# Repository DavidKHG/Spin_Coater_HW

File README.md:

# Spin_Coater_HW
- Final components for spin coater such as circuit, sensor, display, mechanical design.

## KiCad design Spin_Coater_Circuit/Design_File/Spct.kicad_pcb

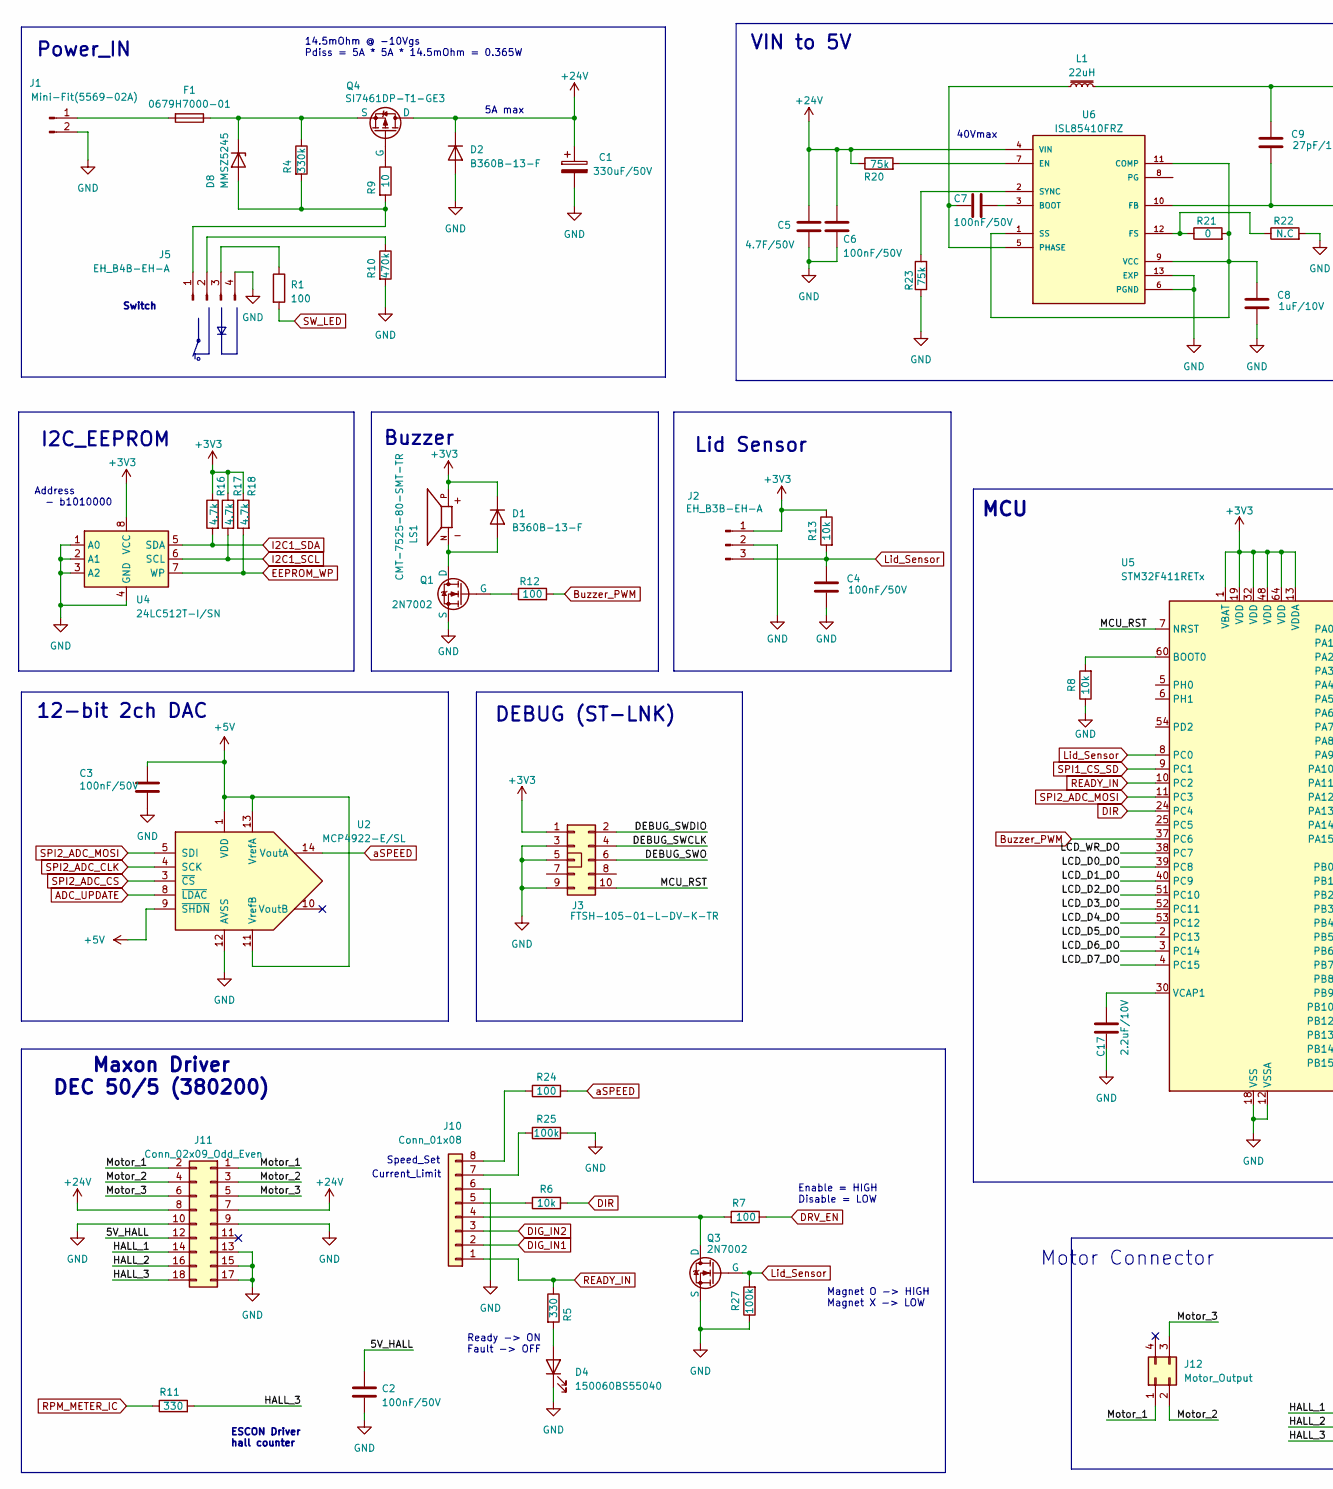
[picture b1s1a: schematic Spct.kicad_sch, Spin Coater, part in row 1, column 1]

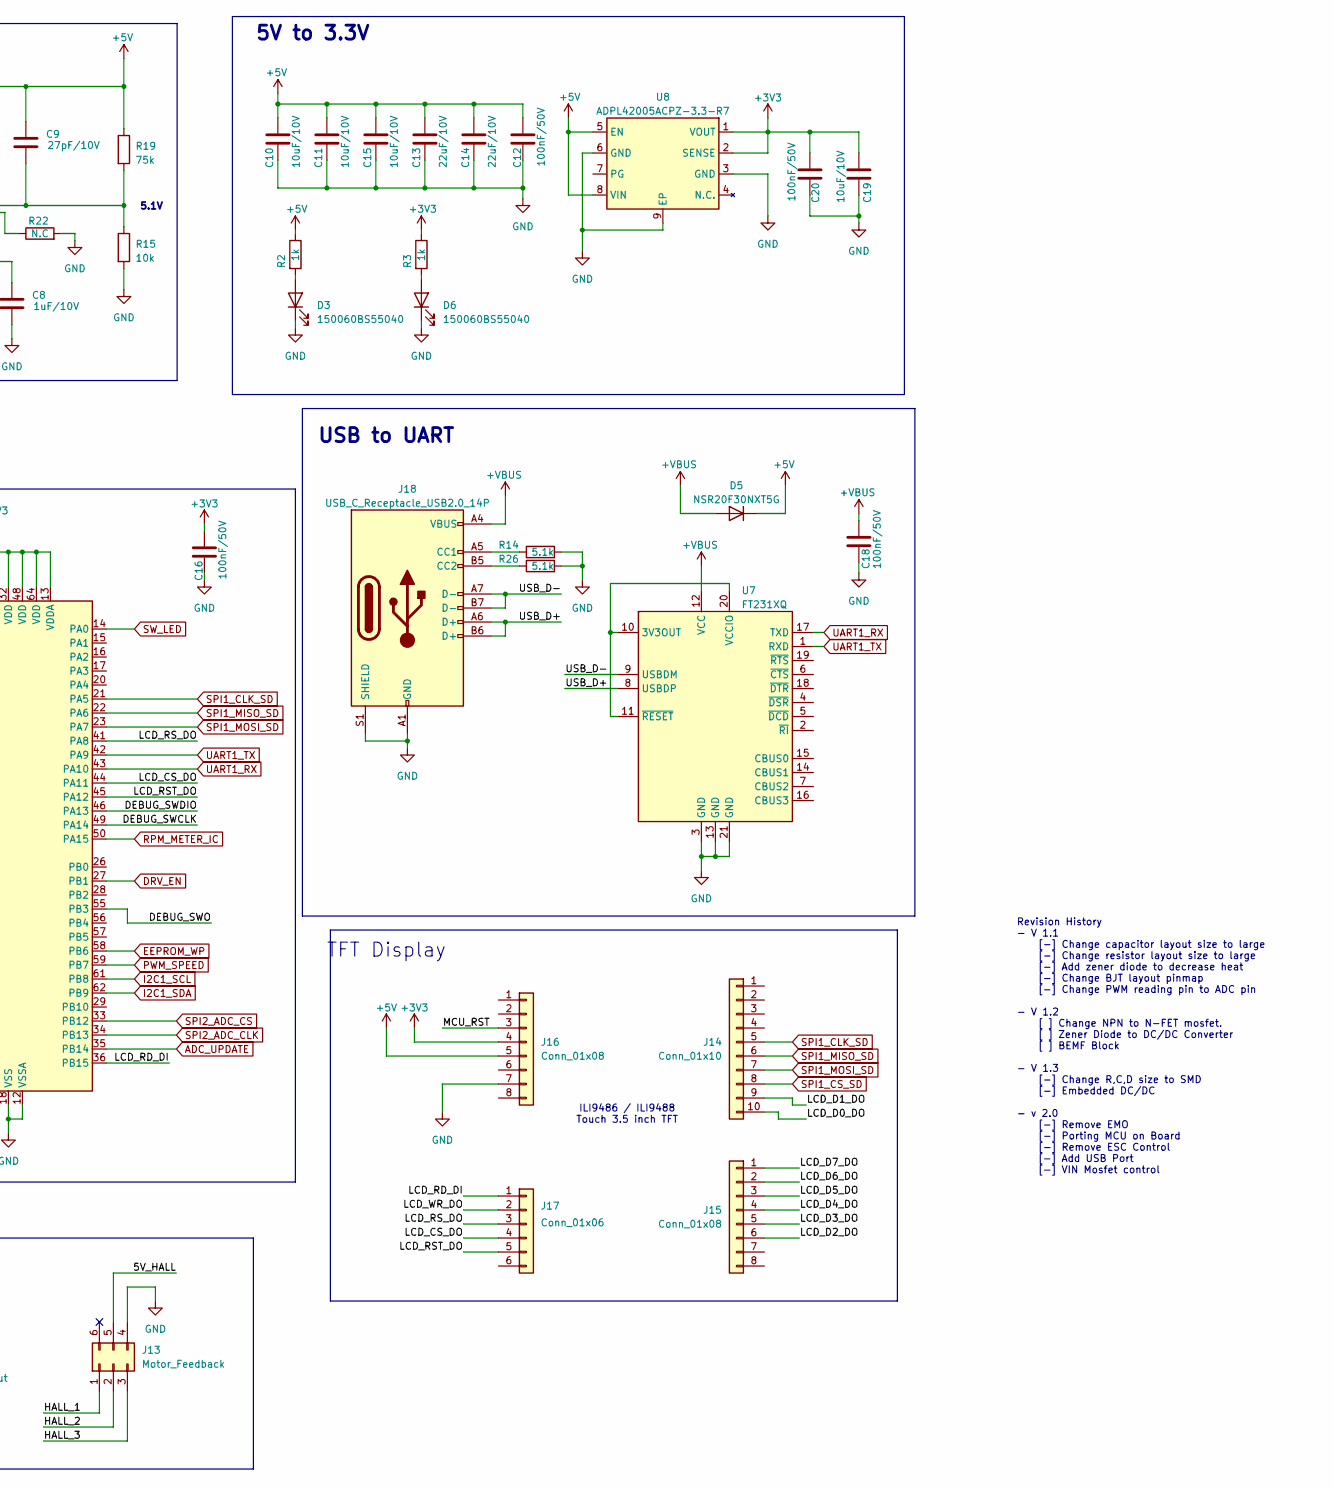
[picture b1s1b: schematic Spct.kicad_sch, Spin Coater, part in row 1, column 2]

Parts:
C1: 330uF/50V; CP_Elec_12.5x12.5
C2, C3, C4, C6, C7, C12, C16, C18, C20: 100nF/50V; C_0603_1608Metric
C5: 4.7F/50V; C_1206_3216Metric
C8: 1uF/10V; C_0603_1608Metric
C9: 27pF/10V; C_0603_1608Metric
C10, C11, C15, C19: 10uF/10V; C_0805_2012Metric
C13, C14: 22uF/10V; C_0805_2012Metric
C17: 2.2uF/10V; C_0603_1608Metric
D1, D2: B360B-13-F; D_SMB
D3, D4, D6: 150060BS55040; LED_0603_1608Metric
D5: NSR20F30NXT5G; DSN2-152AB_ONS
D8: MMSZ5245; D_SOD-123
F1: 0679H7000-01; Fuse_2410_6225_Metric
J1: Mini-Fit(5569-02A); Molex_Mini-Fit_Jr_5569-02A2_2x01_P4.20mm_Horizontal
J2: EH_B3B-EH-A; JST_EH_B3B-EH-A_1x03_P2.50mm_Vertical
J3: FTSH-105-01-L-DV-K-TR; PinHeader_2x05_P1.27mm_Vertical_SMD
J5: EH_B4B-EH-A; JST_EH_B4B-EH-A_1x04_P2.50mm_Vertical
J10, J15, J16: Conn_01x08; PinSocket_1x08_P2.54mm_Vertical
J11: Conn_02x09_Odd_Even; PinSocket_2x09_P2.54mm_Vertical
J12: Motor_Output; Molex_Mini-Fit_Jr_5569-04A2_2x02_P4.20mm_Horizontal
J13: Motor_Feedback; Molex_Micro-Fit_3.0_43045-0621_2x03-1MP_P3.00mm_Horizontal
J14: Conn_01x10; PinSocket_1x10_P2.54mm_Vertical
J17: Conn_01x06; PinSocket_1x06_P2.54mm_Vertical
J18: USB_C_Receptacle_USB2.0_14P; USB_C_Receptacle_G-Switch_GT-USB-7010ASV
L1: 22uH; L_Bourns_SRR6028
LS1: CMT-7525-80-SMT-TR; XDCR_CMT-7525-80-SMT-TR; PARTREV N/A
Q1, Q3: 2N7002; SOT-23
Q4: SI7461DP-T1-GE3; PowerPAK_SO-8_Single
R1, R7, R12, R24: 100; R_0603_1608Metric
R2, R3: 1k; R_0603_1608Metric
R4: 330k; R_0603_1608Metric
R5, R11: 330; R_0603_1608Metric
R6, R8, R13, R15: 10k; R_0603_1608Metric
R9: 10; R_0603_1608Metric
R10: 470k; R_0603_1608Metric
R14, R26: 5.1k; R_0603_1608Metric
R16, R17, R18: 4.7k; R_0603_1608Metric
R19, R20, R23: 75k; R_0603_1608Metric
R21: 0; R_0603_1608Metric
R22: N.C; R_0603_1608Metric
R25, R27: 100k; R_0603_1608Metric
U2: MCP4922-E/SL; SOIC-14_3.9x8.7mm_P1.27mm
U4: 24LC512T-I/SN; SOIC-8_5.3x5.3mm_P1.27mm
U5: STM32F411RETx; LQFP-64_10x10mm_P0.5mm
U6: ISL85410FRZ; SON50P300X300X100-13N_270X200_; PARTREV 8.00
U7: FT231XQ; QFN-20-1EP_4x4mm_P0.5mm_EP2.5x2.5mm
U8: ADPL42005ACPZ-3.3-R7; LFCSP-8-1EP_3x3mm_P0.5mm_EP1.6x2.34mm

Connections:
+3V3: C16.1, C19.1, C20.1, D1.1 (K), J2.1, J3.1, J16.4, LS1.P, R3.1, R13.1, R16.1, R17.1, R18.1, U4.8 (VCC), U5.1 (VBAT), U5.13 (VDDA), U5.19 (VDD), U5.32 (VDD), U5.48 (VDD), U5.64 (VDD), U8.1 (VOUT), U8.2 (SENSE)
+5V: C3.1, C9.1, C10.1, C11.1, C12.1, C13.1, C14.1, C15.1, D5.1 (K), J16.5, L1.2, R2.1, R19.1, U2.1 (VDD), U2.9 (~SHDN), U2.11 (VrefB), U2.13 (VrefA), U8.5 (EN), U8.8 (VIN)
+24V: C1.1, C5.1, C6.1, D2.1 (K), J11.7, J11.8, Q4.5 (D), R20.1, U6.4 (VIN)
+VBUS: C18.1, D5.2 (A), J18.A4 (VBUS), J18.A9 (VBUS), J18.B4 (VBUS), J18.B9 (VBUS), U7.12 (VCC)
/5V_HALL: C2.1, J11.12, J13.5
/DEBUG_SWCLK: J3.4, U5.49 (PA14)
/DEBUG_SWDIO: J3.2, U5.46 (PA13)
/DEBUG_SWO: J3.6, U5.55 (PB3)
/HALL_1: J11.14, J13.1
/HALL_2: J11.16, J13.2
/HALL_3: J11.18, J13.3, R11.2
/LCD_CS_DO: J17.4, U5.44 (PA11)
/LCD_D0_DO: J14.10, U5.39 (PC8)
/LCD_D1_DO: J14.9, U5.40 (PC9)
/LCD_D2_DO: J15.6, U5.51 (PC10)
/LCD_D3_DO: J15.5, U5.52 (PC11)
/LCD_D4_DO: J15.4, U5.53 (PC12)
/LCD_D5_DO: J15.3, U5.2 (PC13)
/LCD_D6_DO: J15.2, U5.3 (PC14)
/LCD_D7_DO: J15.1, U5.4 (PC15)
/LCD_RD_DI: J17.1, U5.36 (PB15)
/LCD_RST_DO: J17.5, U5.45 (PA12)
/LCD_RS_DO: J17.3, U5.41 (PA8)
/LCD_WR_DO: J17.2, U5.38 (PC7)
/MCU_RST: J3.10, J16.3, U5.7 (NRST)
/Motor_1: J11.1, J11.2, J12.1
/Motor_2: J11.3, J11.4, J12.2
/Motor_3: J11.5, J11.6, J12.3
/USB_D+: J18.A6 (D+), J18.B6 (D+), U7.8 (USBDP)
/USB_D-: J18.A7 (D-), J18.B7 (D-), U7.9 (USBDM)
ADC_UPDATE: U2.8 (~LDAC), U5.35 (PB14)
Buzzer_PWM: R12.2, U5.37 (PC6)
DIG_IN1: J10.2
DIG_IN2: J10.3
DIR: R6.2, U5.24 (PC4)
DRV_EN: R7.1, U5.27 (PB1)
EEPROM_WP: R18.2, U4.7 (WP), U5.58 (PB6)
GND: C1.2, C2.2, C3.2, C4.2, C5.2, C6.2, C8.2, C10.2, C11.2, C12.2, C13.2, C14.2, C15.2, C16.2, C17.2, C18.2, C19.2, C20.2, D2.2 (A), D3.1 (K), D4.1 (K), D6.1 (K), J1.2, J2.2, J3.3, J3.5, J3.9, J5.4, J10.6, J11.9, J11.10, J11.13, J11.15, J11.17, J13.4, J16.7, J18.A1 (GND), J18.A12 (GND), J18.B1 (GND), J18.B12 (GND), J18.S1 (SHIELD), Q1.2 (S), Q3.2 (S), R8.1, R10.2, R14.2, R15.2, R22.2, R23.1, R25.2, R26.2, R27.1, U2.12 (AVSS), U4.1 (A0), U4.2 (A1), U4.3 (A2), U4.4 (GND), U5.12 (VSSA), U5.18 (VSS), U5.31 (VSS), U5.47 (VSS), U5.63 (VSS), U6.6 (PGND), U6.13 (EXP), U7.3 (GND), U7.13 (GND), U7.21 (GND), U8.3 (GND), U8.6 (GND), U8.9 (EP)
I2C1_SCL: R17.2, U4.6 (SCL), U5.61 (PB8)
I2C1_SDA: R16.2, U4.5 (SDA), U5.62 (PB9)
Lid_Sensor: C4.1, J2.3, Q3.1 (G), R13.2, R27.2, U5.8 (PC0)
unnamed: D1.2 (A), LS1.N, Q1.3 (D)
unnamed: D3.2 (A), R2.2
unnamed: D4.2 (A), R5.2
unnamed: D6.2 (A), R3.2
unnamed: D8.2 (A), J5.1, R4.2, R9.2
unnamed: D8.1 (K), F1.1, Q4.1 (S), Q4.2 (S), Q4.3 (S), R4.1
unnamed: F1.2, J1.1
unnamed: J5.2, R10.1
unnamed: J5.3, R1.1
unnamed: J10.4, Q3.3 (D), R7.2
unnamed: J10.5, R6.1
unnamed: J10.7, R25.1
unnamed: J10.8, R24.1
unnamed: J18.A5 (CC1), R14.1
unnamed: J18.B5 (CC2), R26.1
unnamed: Q1.1 (G), R12.1
unnamed: Q4.4 (G), R9.1
unnamed: R8.2, U5.60 (BOOT0)
unnamed: C17.1, U5.30 (VCAP1)
unnamed: C7.1, U6.3 (BOOT)
unnamed: C8.1, R21.2, U6.1 (SS), U6.9 (VCC), U6.11 (COMP)
unnamed: R20.2, U6.7 (EN)
unnamed: C9.2, R15.1, R19.2, U6.10 (FB)
unnamed: R21.1, R22.1, U6.12 (FS)
unnamed: C7.2, L1.1, U6.5 (PHASE)
unnamed: R23.2, U6.2 (SYNC)
unnamed: U7.10 (3V3OUT), U7.11 (~RESET), U7.20 (VCCIO)
PWM_SPEED: U5.59 (PB7)
READY_IN: J10.1, R5.1, U5.10 (PC2)
RPM_METER_IC: R11.1, U5.50 (PA15)
SPI1_CLK_SD: J14.5, U5.21 (PA5)
SPI1_CS_SD: J14.8, U5.9 (PC1)
SPI1_MISO_SD: J14.6, U5.22 (PA6)
SPI1_MOSI_SD: J14.7, U5.23 (PA7)
SPI2_ADC_CLK: U2.4 (SCK), U5.34 (PB13)
SPI2_ADC_CS: U2.3 (~CS), U5.33 (PB12)
SPI2_ADC_MOSI: U2.5 (SDI), U5.11 (PC3)
SW_LED: R1.2, U5.14 (PA0)
UART1_RX: U5.43 (PA10), U7.17 (TXD)
UART1_TX: U5.42 (PA9), U7.1 (RXD)
aSPEED: R24.2, U2.14 (VoutA)

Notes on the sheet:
Maxon Driver DEC 50/5 (380200)
40Vmax
Buzzer
Lid Sensor
12-bit 2ch DAC
ESCON Driver hall counter
Address - b1010000
Power_IN
I2C_EEPROM
Speed_Set
USB to UART
MCU
Current_Limit
5V to 3.3V
Revision History - V 1.1 [-] Change capacitor layout size to large [-] Change resistor layout size to large [-] Add zener diode to decrease heat [-] Change BJT layout pinmap [-] Change PWM reading pin to ADC pin - V 1.2 [ ] Change NPN to N-FET mosfet. [ ] Zener Diode to DC/DC Converter [ ] BEMF Blo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
Ready -> ON Fault -> OFF
5A max
Motor Connector
Enable = HIGH Disable = LOW
5.1V
Magnet O -> HIGH Magnet X -> LOW
DEBUG (ST-LNK)
TFT Display
Switch
14.5mOhm @ -10Vgs Pdiss = 5A * 5A * 14.5mOhm = 0.365W
ILI9486 / ILI9488 Touch 3.5 inch TFT
VIN to 5V

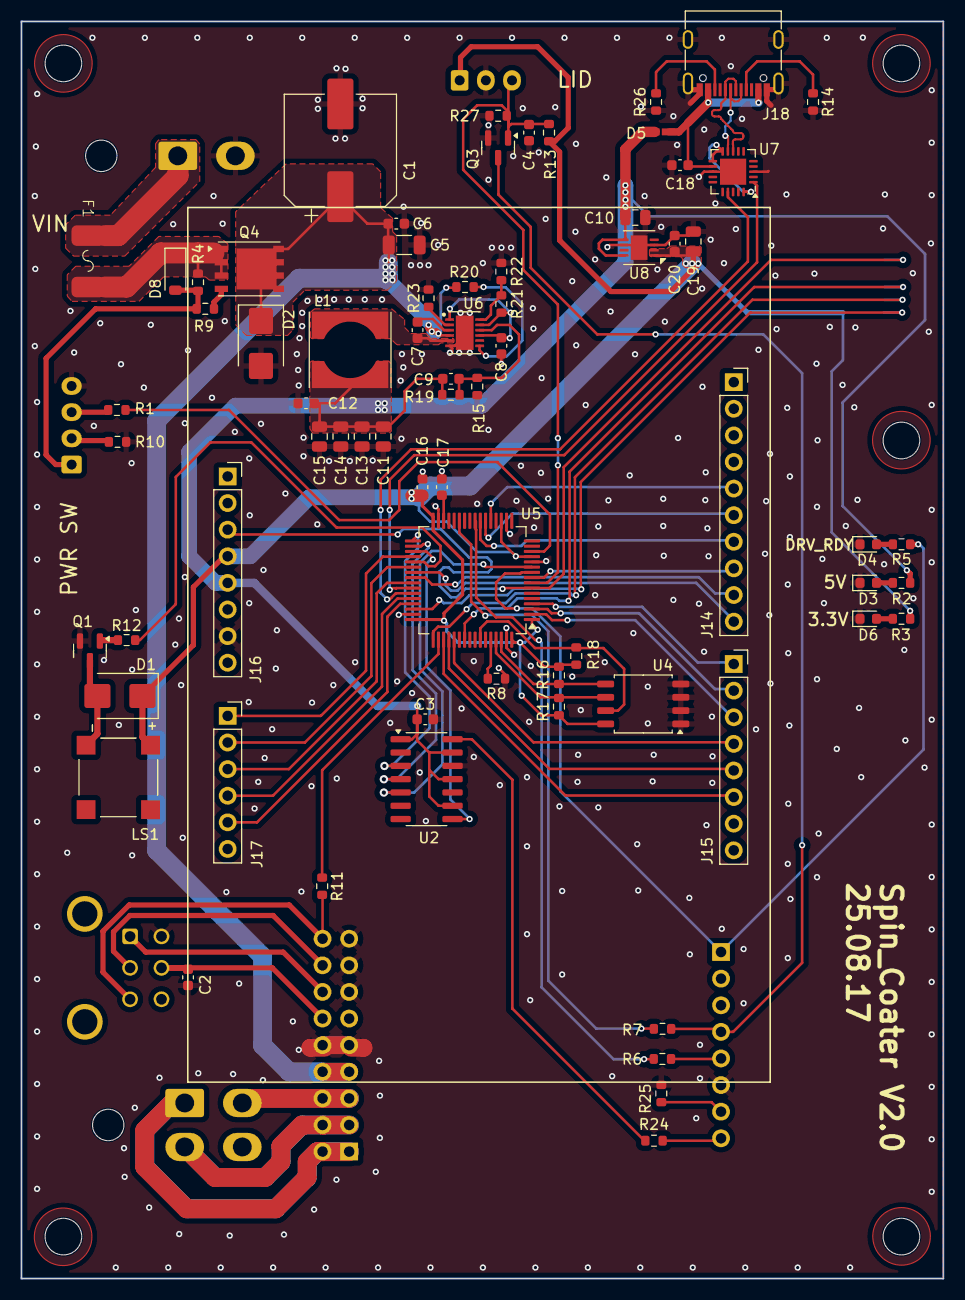
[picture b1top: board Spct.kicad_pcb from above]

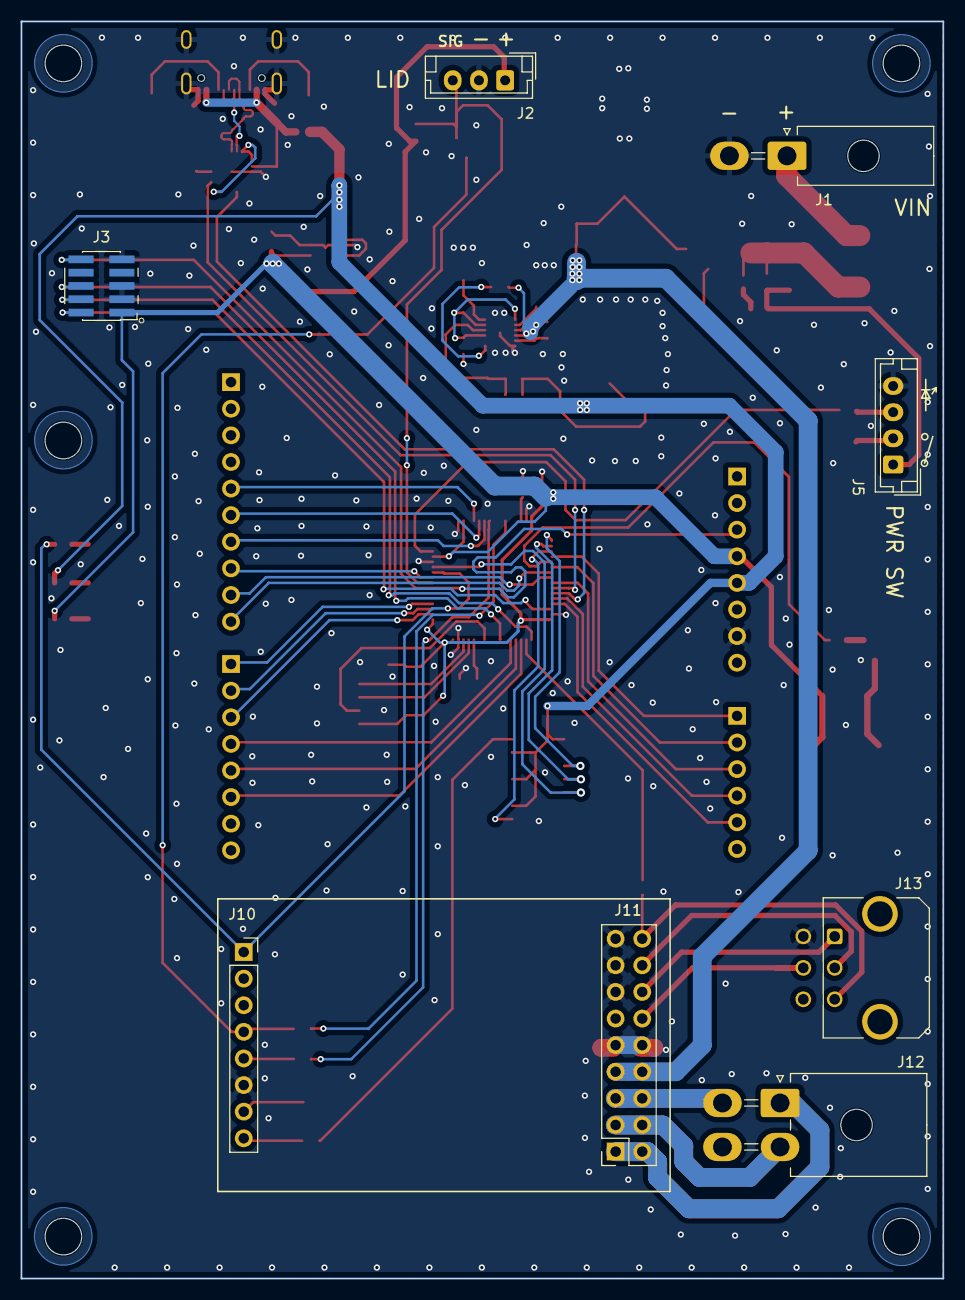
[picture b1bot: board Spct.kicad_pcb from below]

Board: 2 copper layers, 88.0 x 120.0 mm, 79 parts (8 on the bottom side), 79 nets.

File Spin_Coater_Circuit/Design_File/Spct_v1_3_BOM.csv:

Reference,Value,Datasheet,Footprint,Qty,DNP,MANUFACTURER,Manufacturer
C1,330uF/50V,https://www.mouser.com/datasheet/2/420/Chemi_Con_MVHRA_e-331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,Custom_Library:CP_Elec_12.5x12.5,1,,,Chemi-con/EMVH500ARA331MKG5S
"C2,C3,C4,C6,C7,C12",100nF/50V,~,Capacitor_SMD:C_0603_1608Metric,6,,,Samsung/CL10B104MB8NNNC
C5,4.7F/50V,~,Capacitor_SMD:C_1206_3216Metric,1,,,KEMET/C1206C475K5PAC
C8,1uF/10V,~,Capacitor_SMD:C_0603_1608Metric,1,,,Taiyoyuden/LMK107B7105MA-T
C9,27pF/10V,~,Capacitor_SMD:C_0603_1608Metric,1,,,KEMET/C0603C270J8HACTU
"C10,C11,C15",10uF/10V,https://www.mouser.com/datasheet/2/585/MLCC-1837944.pdf,Capacitor_SMD:C_0805_2012Metric,3,,,Samsung/CL21A106KPFNNNF
"C13,C14",22uF/10V,https://www.mouser.com/datasheet/2/585/MLCC-1837944.pdf,Capacitor_SMD:C_0805_2012Metric,2,,,Samsung/CL21A226MPQNNNE
"D1,D2",B360B-13-F,https://www.mouser.com/datasheet/2/115/DIOD_S_A0004140824_1-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,Diode_SMD:D_SMB,2,,,
D3,MM3Z3V3T1G,~,Custom_Library:D_SOD-323-2,1,,,Onsemni
D4,150060BS55040,https://www.we-online.com/components/products/datasheet/1500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,LED_SMD:LED_0603_1608Metric,1,,,Würth Elektronik
F1,0679H5000-01,https://www.mouser.com/datasheet/2/643/ds_cp_0679h_series-12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,Custom_Library:Fuse_2410_6225_Metric,1,,,
"J1,J4,J6,J8,J9",EH_B2B-EH-A,~,Connector_JST:JST_EH_B2B-EH-A_1x02_P2.50mm_Vertical,5,,,JST
J2,EH_B3B-EH-A,~,Connector_JST:JST_EH_B3B-EH-A_1x03_P2.50mm_Vertical,1,,,JST
J3,EH_B8B-EH-A,~,Connector_JST:JST_EH_B8B-EH-A_1x08_P2.50mm_Vertical,1,,,JST
J5,EH_B4B-EH-A,~,Connector_JST:JST_EH_B4B-EH-A_1x04_P2.50mm_Vertical,1,,,JST
J7,EH_B6B-EH-A,~,Connector_JST:JST_EH_B6B-EH-A_1x06_P2.50mm_Vertical,1,,,JST
L1,22uH,~,Custom_Library:L_Bourns_SRR6028,1,,,Bourns/SRR6028-220Y
LS1,CMT-7525-80-SMT-TR,,Custom_Library:XDCR_CMT-7525-80-SMT-TR,1,,CUI Inc.,
"Q1,Q2,Q3",2N7002,https://ngspice.sourceforge.io/docs/ngspice-html-manual/manu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,Package_TO_SOT_SMD:SOT-23,3,,,
"R1,R4,R7,R9,R12",100,~,Resistor_SMD:R_0603_1608Metric,5,,,
"R2,R19,R20,R23",75k,~,Resistor_SMD:R_0603_1608Metric,4,,,
"R3,R6,R8,R13,R14,R15",10k,~,Resistor_SMD:R_0603_1608Metric,6,,,
"R5,R11",330,~,Resistor_SMD:R_0603_1608Metric,2,,,
"R10,R16,R17,R18",4.7k,~,Resistor_SMD:R_0603_1608Metric,4,,,
R21,0,~,Resistor_SMD:R_0603_1608Metric,1,,,
U1,NUCLEO-F411RE,,Module:ST_NUCLEO-F401RE,1,,STMicroelectronics,
 ->,2x19 2.54mm pitch Box Header,,,2,,,
U2,MCP4922-E/SL,https://ww1.microchip.com/downloads/aemDocuments/documents/O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,Package_SO:SOIC-14_3.9x8.7mm_P1.27mm,1,,,Microchips
U3,367661,,Connector_Pin:MAXON_DRV,1,,,
 ->,1x8 2.54mm pitch Box Header,,,1,,,
 ->,1x9 2.54mm pitch Box Header,,,1,,,
U4,24LC512T-I/SN,http://ww1.microchip.com/downloads/en/DeviceDoc/21754M.pdf,Package_SO:SOIC-8_5.275x5.275mm_P1.27mm,1,,,Microchips
U6,ISL85410FRZ,https://www.mouser.com/datasheet/2/698/REN_isl85410_DST_2019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,Custom_Library:SON50P300X300X100-13N_270X200_,1,,RENESAS,

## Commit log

2023-06-29 Circuit Design ver 1.0
2023-07-01 Change Ver1.1
2023-07-01 add schematics print
2023-07-01 add gitignore
2023-07-01 modify gitignore for ki-cad
2023-07-01 modify gitignore for mac
2023-07-28 Circuit version 1.2
2024-05-19 Spin coater ver1.3
2025-08-03 version 2.0 circuit init
2025-08-11 Place Arduino pinout / Drv socket
2025-08-17 finalize layout
2025-08-18 Output setup & layout minor fix
2025-08-22 modify final output
